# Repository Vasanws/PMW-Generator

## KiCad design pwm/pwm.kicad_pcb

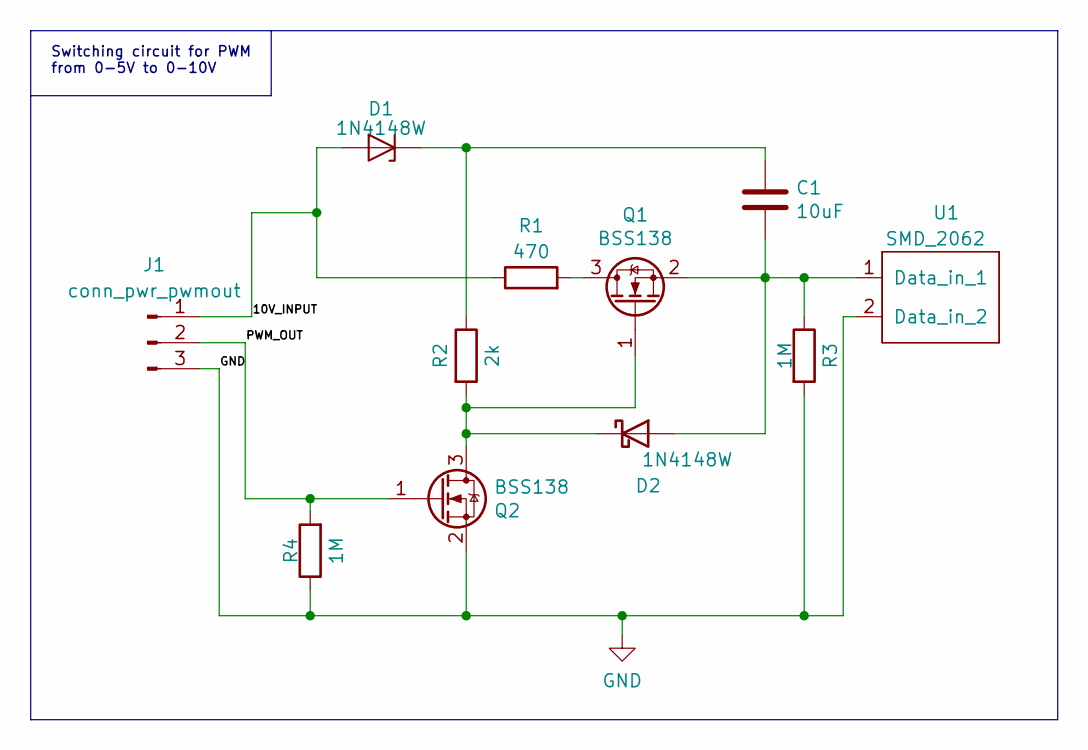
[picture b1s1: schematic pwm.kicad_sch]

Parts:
C1: 10uF; C_0805_2012Metric
D1, D2: 1N4148W; D_SOD-123
J1: conn_pwr_pwmout; PinHeader_1x03_P2.54mm_Vertical
Q1, Q2: BSS138; SOT-23
R1: 470; R_0805_2012Metric
R2: 2k; R_0805_2012Metric
R3, R4: 1M; R_0805_2012Metric
U1: SMD_2062; LEDSMD2062

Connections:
/10V_INPUT: D1.2 (A), J1.1, R1.1
/PWM_OUT: J1.2, Q2.1 (G), R4.2
GND: J1.3, Q2.2 (S), R3.2, R4.1, U1.2 (Data_in)
unnamed: C1.1, D1.1 (K), R2.1
unnamed: C1.2, D2.2 (A), Q1.2 (S), R3.1, U1.1 (Data_in)
unnamed: D2.1 (K), Q1.1 (G), Q2.3 (D), R2.2
unnamed: Q1.3 (D), R1.2

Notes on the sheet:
Switching circuit for PWM from 0-5V to 0-10V

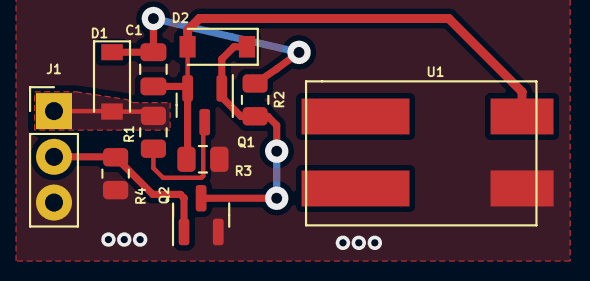
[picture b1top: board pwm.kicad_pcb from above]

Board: 2 copper layers, 11 parts (0 on the bottom side), 7 nets.

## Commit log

2022-07-04 PWM Generator
